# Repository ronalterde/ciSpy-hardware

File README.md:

# ciSpy Hardware
Board originally designed to fit on top of the [Carambola 2](http://www.8devices.com/products/carambola-2) development board.

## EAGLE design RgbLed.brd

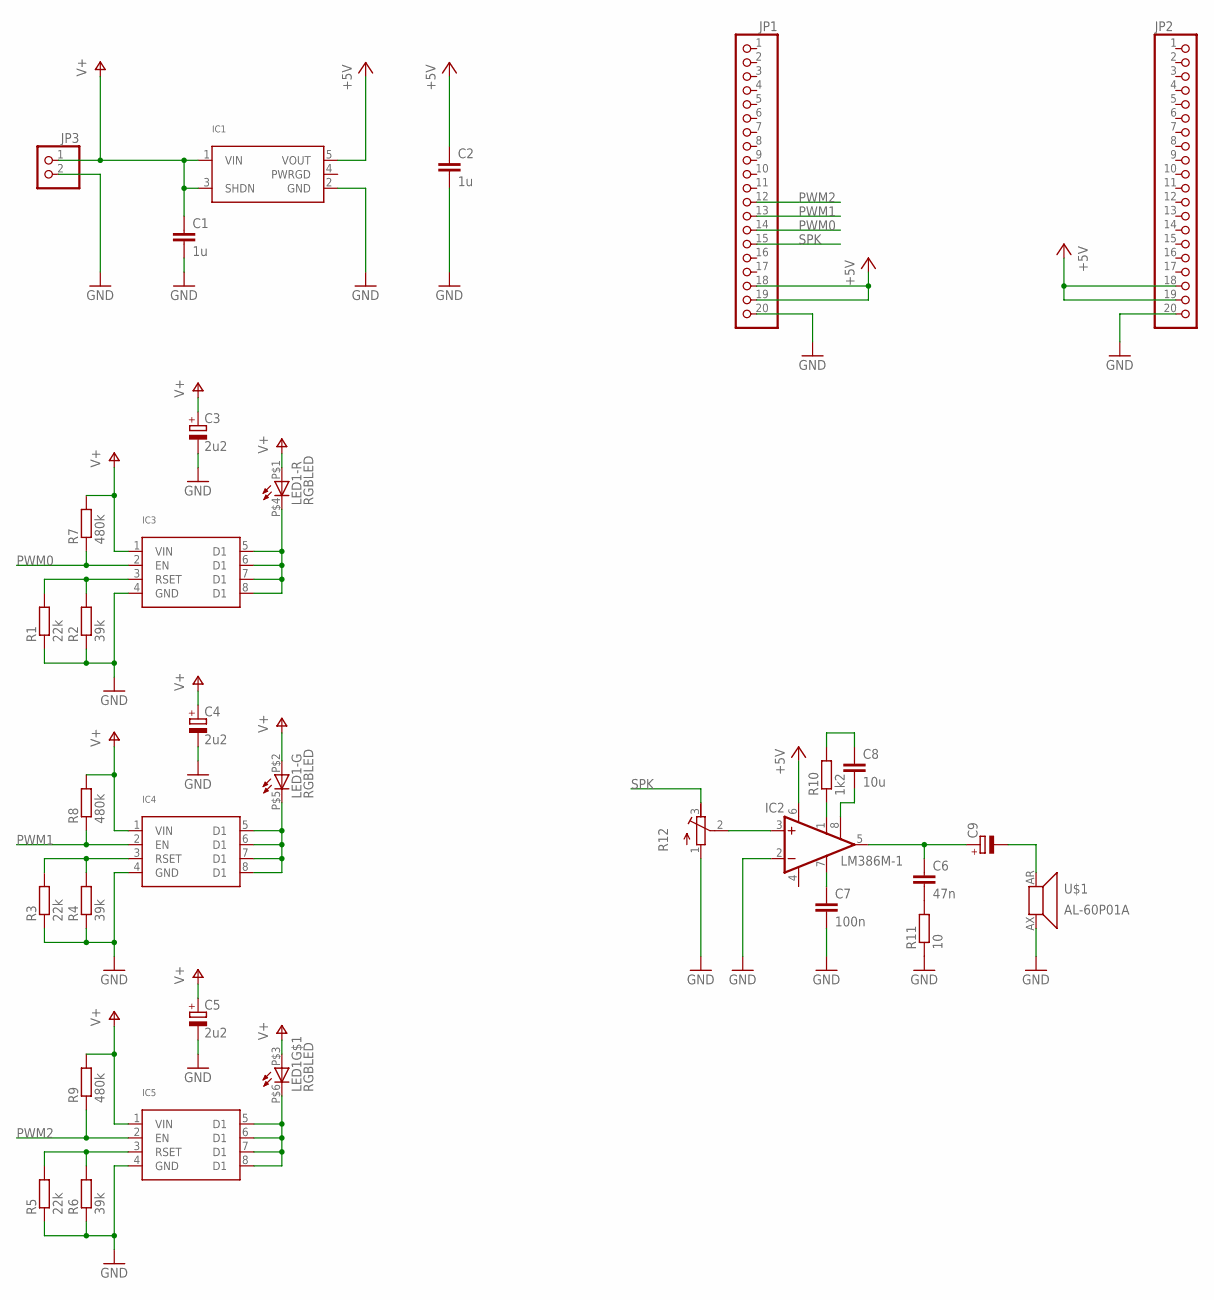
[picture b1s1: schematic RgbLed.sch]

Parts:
C1, C2: 1u; C0805
C3, C4, C5: 2u2; PANASONIC_B
C6: 47n; C0805
C7: 100n; C0805
C8: 10u; C0805
C9: CPOL-EUE; PANASONIC_E
IC1: MCP1755TSOT; SOT23-5L
IC2: LM386M-1; SO08
IC3, IC4, IC5: MIC4802YME; SO8-COOL
JP1, JP2: PINHD-1X20; 1X20
JP3: PINHD-1X2; 1X02
LED1: RGBLED
R1, R3, R5: 22k; R0805
R2, R4, R6: 39k; R0805
R7, R8, R9: 480k; R0805
R10: 1k2; R0805
R11: 10; R0805
R12: R-TRIMM; ACP6SMD
U$1: AL-60P01A

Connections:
+5V: C2.1, IC1.5 (VOUT), IC2.6 (VS), JP1.18, JP1.19, JP2.18, JP2.19
GND: C1.2, C2.2, C3.-, C4.-, C5.-, C7.2, IC1.2 (GND), IC2.2 (-IN), IC2.4 (GND), IC3.4 (GND), IC4.4 (GND), IC5.4 (GND), JP1.20, JP2.20, JP3.2, R1.1, R2.1, R3.1, R4.1, R5.1, R6.1, R11.1, R12.1 (A), U$1.AX (2)
unnamed: IC3.3 (RSET), R1.2, R2.2
unnamed: IC4.3 (RSET), R3.2, R4.2
unnamed: IC5.3 (RSET), R5.2, R6.2
unnamed: IC3.5 (D1), IC3.6 (D1), IC3.7 (D1), IC3.8 (D1), LED1.P$4 (C)
unnamed: IC4.5 (D1), IC4.6 (D1), IC4.7 (D1), IC4.8 (D1), LED1.P$5 (C)
unnamed: IC5.5 (D1), IC5.6 (D1), IC5.7 (D1), IC5.8 (D1), LED1.P$6 (C)
unnamed: IC2.1 (GAIN), R10.1
unnamed: C8.2, IC2.8 (GAIN)
unnamed: C8.1, R10.2
unnamed: C7.1, IC2.7 (BYPASS)
unnamed: C6.2, R11.2
unnamed: C6.1, C9.+, IC2.5 (OUT)
unnamed: C9.-, U$1.AR (1)
unnamed: IC2.3 (+IN), R12.2 (S)
PWM0: IC3.2 (EN), JP1.14, R7.1
PWM1: IC4.2 (EN), JP1.13, R8.1
PWM2: IC5.2 (EN), JP1.12, R9.1
SPK: JP1.15, R12.3 (E)
V+: C1.1, C3.+, C4.+, C5.+, IC1.1 (VIN), IC1.3 (SHDN), IC3.1 (VIN), IC4.1 (VIN), IC5.1 (VIN), JP3.1, LED1.P$1 (A), LED1.P$2 (A), LED1.P$3 (A), R7.2, R8.2, R9.2

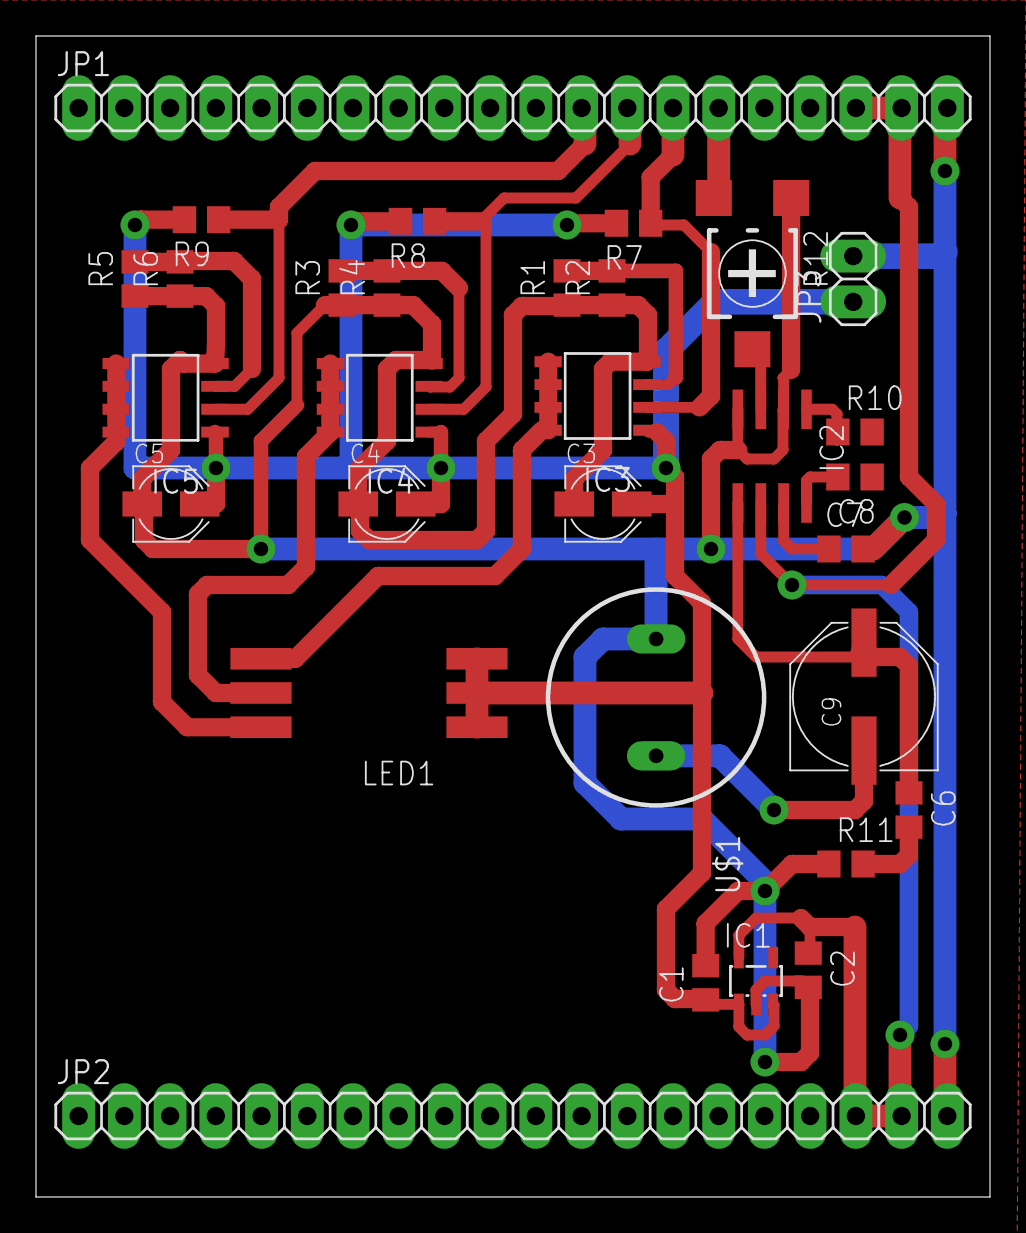
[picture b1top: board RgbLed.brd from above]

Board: 2 copper layers, 53.0 x 64.5 mm, 31 parts (0 on the bottom side), 21 nets.

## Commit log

2017-05-13 Add current project snapshot
